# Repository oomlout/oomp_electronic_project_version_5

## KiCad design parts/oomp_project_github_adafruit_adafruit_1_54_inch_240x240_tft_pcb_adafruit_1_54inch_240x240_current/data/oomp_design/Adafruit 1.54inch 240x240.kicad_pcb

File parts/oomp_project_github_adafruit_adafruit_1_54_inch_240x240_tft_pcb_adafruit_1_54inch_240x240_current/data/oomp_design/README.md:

# OOMP KiCad design copy

Open `Adafruit 1.54inch 240x240.kicad_pro` (or the `.kicad_pcb` / `.kicad_sch`) in KiCad. Local OOMP libraries are under `libraries/`. Original inputs are preserved in [../original/](../original/).

Only verified unchanged installed KiCad defaults were renamed. Modified, custom, unmatched and unavailable items remain unchanged. Soldering variants are never swapped during conversion. Existing pad coordinates, nets and UUIDs are preserved.

See [conversion_report.yaml](conversion_report.yaml) for every conversion and skip. Copy this directory before editing; regeneration refuses to overwrite edited design files.

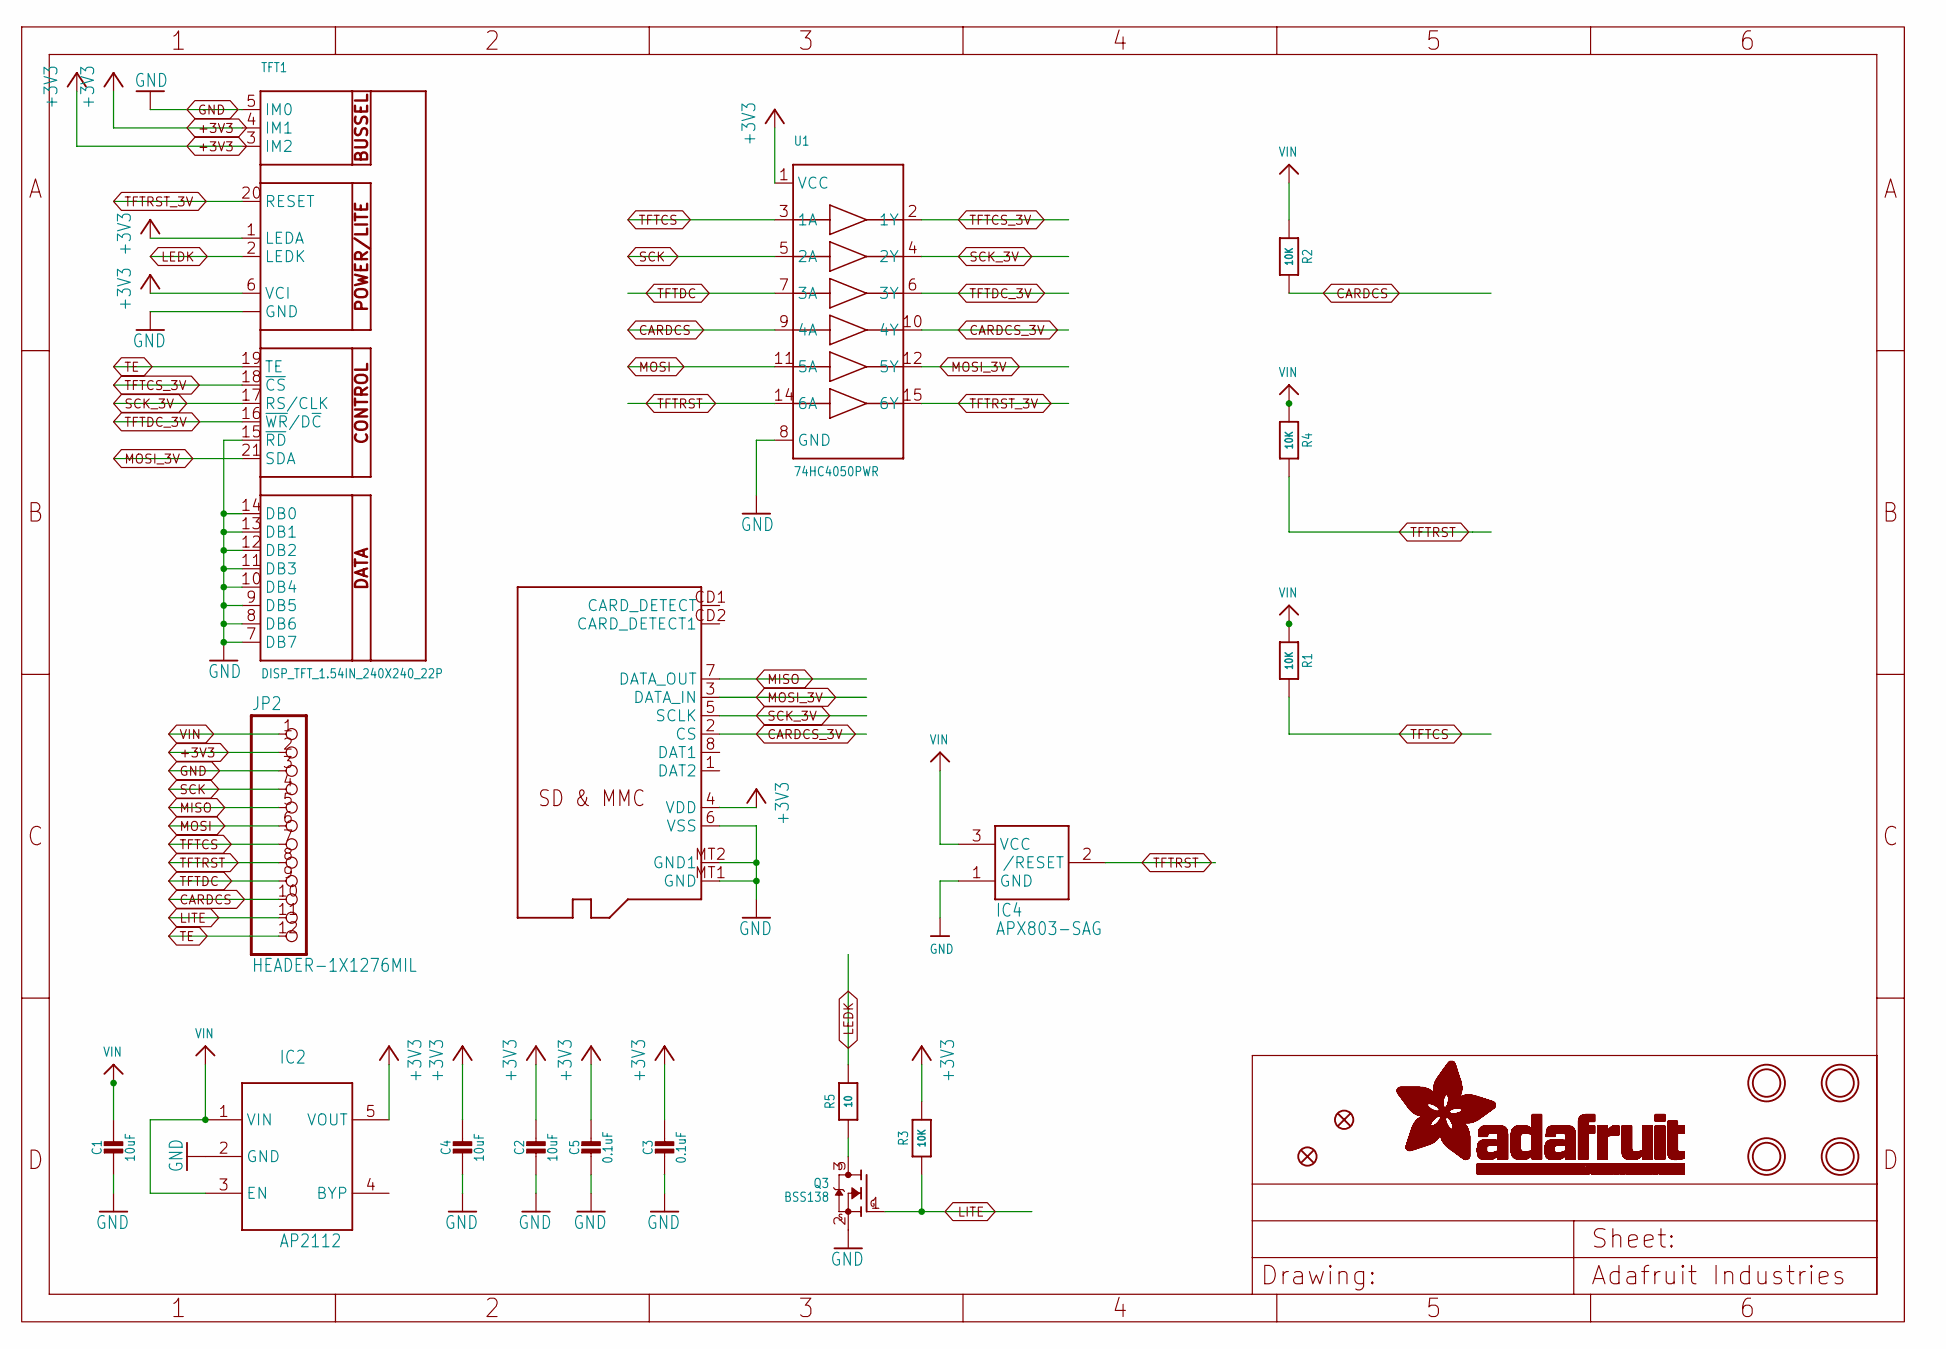
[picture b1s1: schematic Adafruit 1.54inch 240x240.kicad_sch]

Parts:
C1, C2, C4: 10uF; 0805-NO
C3, C5: 0.1uF; 0603-NO
IC2: AP2112; SOT23-5L
IC4: APX803-SAG; SOT23
JP2: HEADER-1X1276MIL; 1X12_ROUND_76MIL
Q2: MICROSD
Q3: BSS138; SOT23-WIDE
R1, R2, R3, R4: 10K; 0603-NO
R5: 10; 0603-NO
TFT1: DISP_TFT_1.54IN_240X240_22P; TFT_1.54IN_240X240_22PIN
U1: 74HC4050PWR; TSSOP16
U$4, U$5: FIDUCIAL_1MM
U$7, U$8, U$9, U$10: MOUNTINGHOLE2.5; MOUNTINGHOLE_2.5_PLATED

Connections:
+3V3: C2.1, C3.1, C4.1, C5.1, IC2.5 (VOUT), JP2.2, Q2.4 (VDD), R3.2, TFT1.1 (LEDA), TFT1.3 (IM2), TFT1.4 (IM1), TFT1.6 (VCI), U1.1 (VCC)
CARDCS: JP2.10, R2.1, U1.9 (4A)
CARDCS_3V: Q2.2 (CS), U1.10 (4Y)
GND: C1.2, C2.2, C3.2, C4.2, C5.2, IC2.2 (GND), IC4.1 (GND), JP2.3, Q2.6 (VSS), Q2.MT1 (GND), Q2.MT2 (GND1), Q3.2 (S), TFT1.5 (IM0), TFT1.7 (DB7), TFT1.8 (DB6), TFT1.9 (DB5), TFT1.10 (DB4), TFT1.11 (DB3), TFT1.12 (DB2), TFT1.13 (DB1), TFT1.14 (DB0), TFT1.15 (~RD), TFT1.22 (GND), TFT1.SUPPORT1 (GND), TFT1.SUPPORT2 (GND), U1.8 (GND)
LEDK: R5.2, TFT1.2 (LEDK)
LITE: JP2.11, Q3.1 (G), R3.1
MISO: JP2.5, Q2.7 (DATA_OUT)
MOSI: JP2.6, U1.11 (5A)
MOSI_3V: Q2.3 (DATA_IN), TFT1.21 (SDA), U1.12 (5Y)
unnamed: Q3.3 (D), R5.1
SCK: JP2.4, U1.5 (2A)
SCK_3V: Q2.5 (SCLK), TFT1.17 (RS/CLK), U1.4 (2Y)
TE: JP2.12, TFT1.19 (TE)
TFTCS: JP2.7, R1.1, U1.3 (1A)
TFTCS_3V: TFT1.18 (~CS), U1.2 (1Y)
TFTDC: JP2.9, U1.7 (3A)
TFTDC_3V: TFT1.16 (~WR/D~C), U1.6 (3Y)
TFTRST: IC4.2 (/RESET), JP2.8, R4.1, U1.14 (6A)
TFTRST_3V: TFT1.20 (RESET), U1.15 (6Y)
VIN: C1.1, IC2.1 (VIN), IC2.3 (EN), IC4.3 (VCC), JP2.1, R1.2, R2.2, R4.2

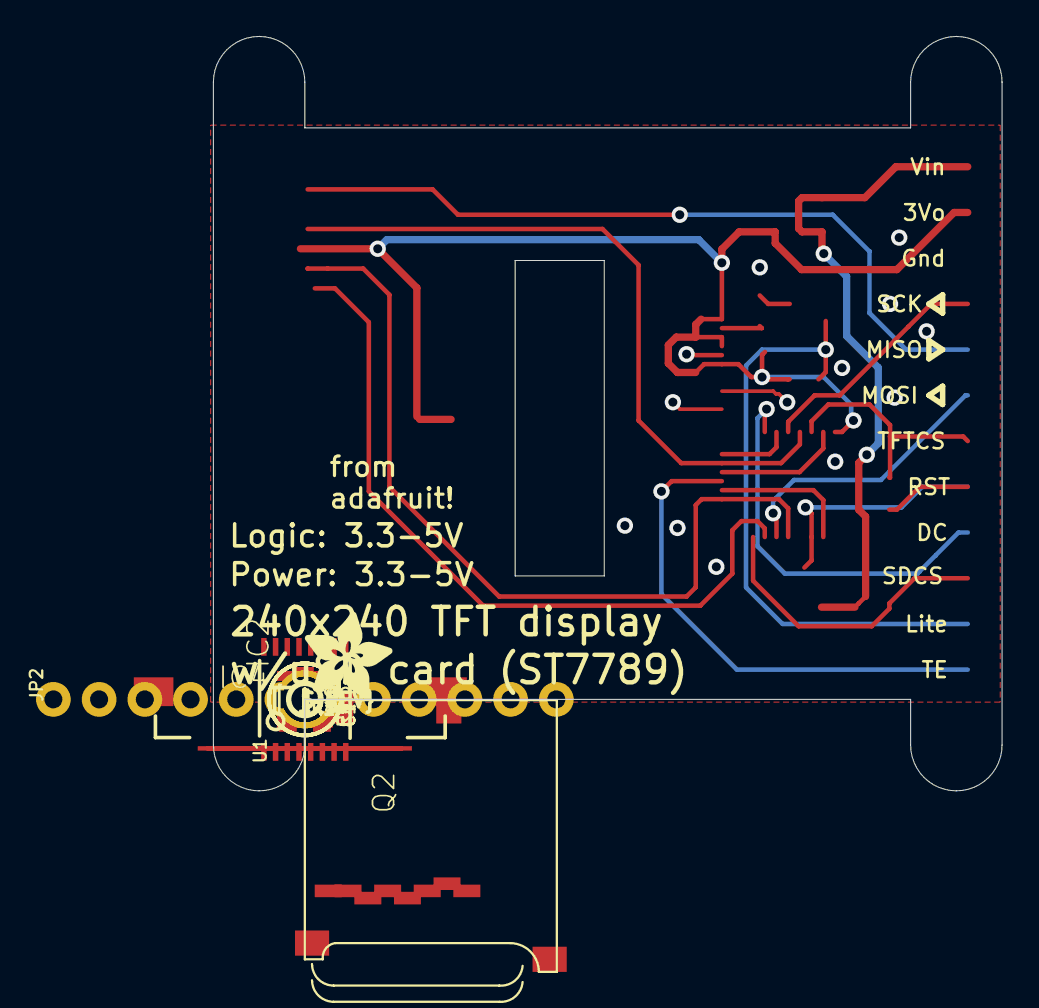
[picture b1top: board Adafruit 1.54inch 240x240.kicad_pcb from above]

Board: 16 copper layers, 43.8 x 41.9 mm, 25 parts (1 on the bottom side), 20 nets.

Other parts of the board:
U$1: ADAFRUIT_5MM
U$2: PCBFEAT-REV-040

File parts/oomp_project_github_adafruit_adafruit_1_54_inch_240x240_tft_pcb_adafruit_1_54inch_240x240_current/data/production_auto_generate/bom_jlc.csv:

Comment,Designator,Footprint,LCSC Part #
,JP2,Adafruit 1.54inch 240x240-import-fps:1X12_ROUND_76MIL,C7501588
,U$1,Adafruit 1.54inch 240x240-import-fps:ADAFRUIT_5MM,
,U$2,Adafruit 1.54inch 240x240-import-fps:PCBFEAT-REV-040,
0.1uF,"C3,C5",Adafruit 1.54inch 240x240-import-fps:0603-NO,C14663
10,R5,Adafruit 1.54inch 240x240-import-fps:0603-NO,C22859
10K,"R1,R2,R3,R4",Adafruit 1.54inch 240x240-import-fps:0603-NO,C98220
10uF,"C1,C2,C4",Adafruit 1.54inch 240x240-import-fps:0805-NO,
74HC4050PWR,U1,Adafruit 1.54inch 240x240-import-fps:TSSOP16,
AP2112,IC2,Adafruit 1.54inch 240x240-import-fps:SOT23-5L,
APX803-SAG,IC4,Adafruit 1.54inch 240x240-import-fps:SOT23,
BSS138,Q3,Adafruit 1.54inch 240x240-import-fps:SOT23-WIDE,C52895
DISP_TFT_1.54IN_240X240_22P,TFT1,Adafruit 1.54inch 240x240-import-fps:TFT_1.54IN_240X240_22PIN,
FIDUCIAL_1MM,"U$4,U$5",Adafruit 1.54inch 240x240-import-fps:FIDUCIAL_1MM,
MICROSD,Q2,Adafruit 1.54inch 240x240-import-fps:MICROSD,

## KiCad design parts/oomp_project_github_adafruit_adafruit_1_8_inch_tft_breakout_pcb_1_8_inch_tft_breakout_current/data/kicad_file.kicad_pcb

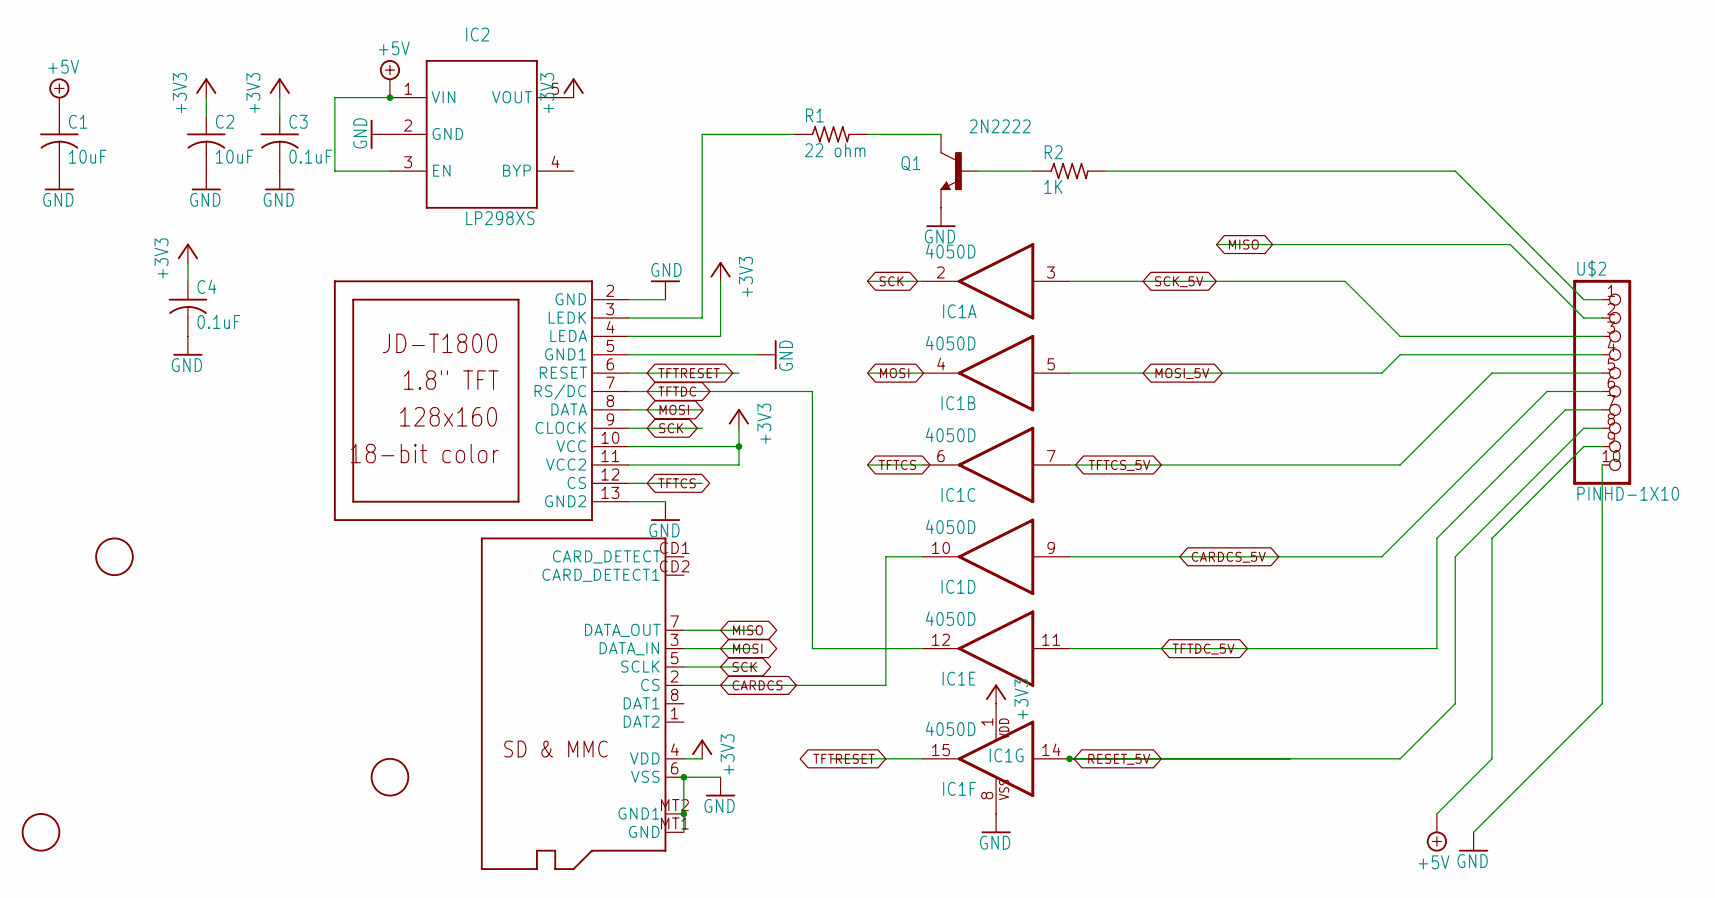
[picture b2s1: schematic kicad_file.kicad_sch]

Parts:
C1, C2: 10uF; C0805K
C3, C4: 0.1uF; C0805K
IC1: 4050D; SO16
IC2: LP298XS; SOT23-5L
Q1: 2N2222; SOT23-BEC
Q2: MICROSD
R1: 22 ohm; R0805
R2: 1K; R0805
U$1: JD-T1800
U$2: PINHD-1X10; 1X10-BIG
U$3, U$4, U$5: FIDUCIAL; FIDUCIAL_1MM

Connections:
+3V3: C2.1, C3.1, C4.1, IC1.1 (VDD), IC2.5 (VOUT), Q2.4 (VDD), U$1.4 (LEDA), U$1.10 (VCC), U$1.11 (VCC2)
+5V: C1.1, IC2.1 (VIN), IC2.3 (EN), U$2.9
CARDCS: IC1.10 (O), Q2.2 (CS)
CARDCS_5V: IC1.9 (I), U$2.6
GND: C1.2, C2.2, C3.2, C4.2, IC1.8 (VSS), IC2.2 (GND), Q1.E, Q2.6 (VSS), Q2.MT1 (GND), Q2.MT2 (GND1), U$1.2 (GND), U$1.5 (GND1), U$1.13 (GND2), U$2.10
MISO: Q2.7 (DATA_OUT), U$2.2
MOSI: IC1.4 (O), Q2.3 (DATA_IN), U$1.8 (DATA)
MOSI_5V: IC1.5 (I), U$2.4
unnamed: Q1.B, R2.1
unnamed: R1.1, U$1.3 (LEDK)
unnamed: Q1.C, R1.2
unnamed: R2.2, U$2.1
RESET_5V: IC1.14 (I), U$2.8
SCK: IC1.2 (O), Q2.5 (SCLK), U$1.9 (CLOCK)
SCK_5V: IC1.3 (I), U$2.3
TFTCS: IC1.6 (O), U$1.12 (CS)
TFTCS_5V: IC1.7 (I), U$2.5
TFTDC: IC1.12 (O), U$1.7 (RS/DC)
TFTDC_5V: IC1.11 (I), U$2.7
TFTRESET: IC1.15 (O), U$1.6 (RESET)

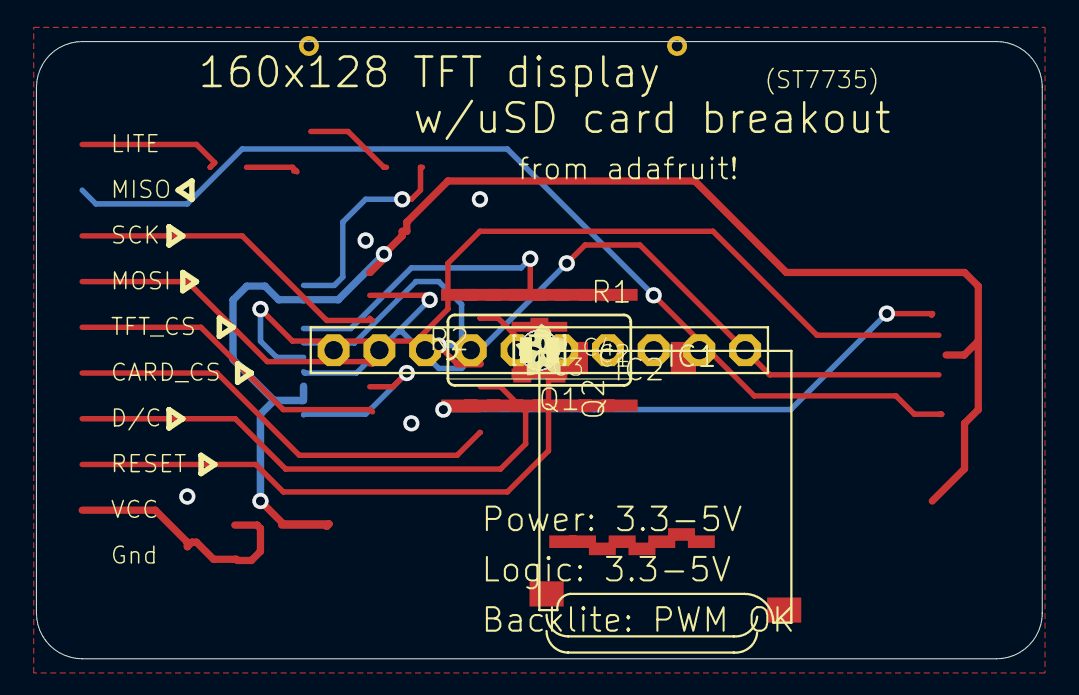
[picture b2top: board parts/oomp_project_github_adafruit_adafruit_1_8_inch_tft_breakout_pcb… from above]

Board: 16 copper layers, 55.9 x 34.3 mm, 20 parts (1 on the bottom side), 20 nets.

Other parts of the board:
U$6: ADAFRUIT200MIL
UNK_HOLE_0: dummyfp0
UNK_HOLE_1: dummyfp1
UNK_HOLE_2: dummyfp2
UNK_HOLE_3: dummyfp3

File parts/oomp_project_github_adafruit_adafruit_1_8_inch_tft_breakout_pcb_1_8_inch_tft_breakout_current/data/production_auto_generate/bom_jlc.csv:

Comment,Designator,Footprint,LCSC Part #
,U$6,jdt1800-bob-import-fps:ADAFRUIT200MIL,
0.1uF,"C3,C4",jdt1800-bob-import-fps:C0805K,
10uF,"C1,C2",jdt1800-bob-import-fps:C0805K,
1K,R2,jdt1800-bob-import-fps:R0805,C17513
22 ohm,R1,jdt1800-bob-import-fps:R0805,C2907310
2N2222,Q1,jdt1800-bob-import-fps:SOT23-BEC,
4050D,IC1,jdt1800-bob-import-fps:SO16,
FIDUCIAL,"U$3,U$4,U$5",jdt1800-bob-import-fps:FIDUCIAL_1MM,
JD-T1800,U$1,jdt1800-bob-import-fps:JD-T1800,
LP298XS,IC2,jdt1800-bob-import-fps:SOT23-5L,
MICROSD,Q2,jdt1800-bob-import-fps:MICROSD,
PINHD-1X10,U$2,jdt1800-bob-import-fps:1X10-BIG,

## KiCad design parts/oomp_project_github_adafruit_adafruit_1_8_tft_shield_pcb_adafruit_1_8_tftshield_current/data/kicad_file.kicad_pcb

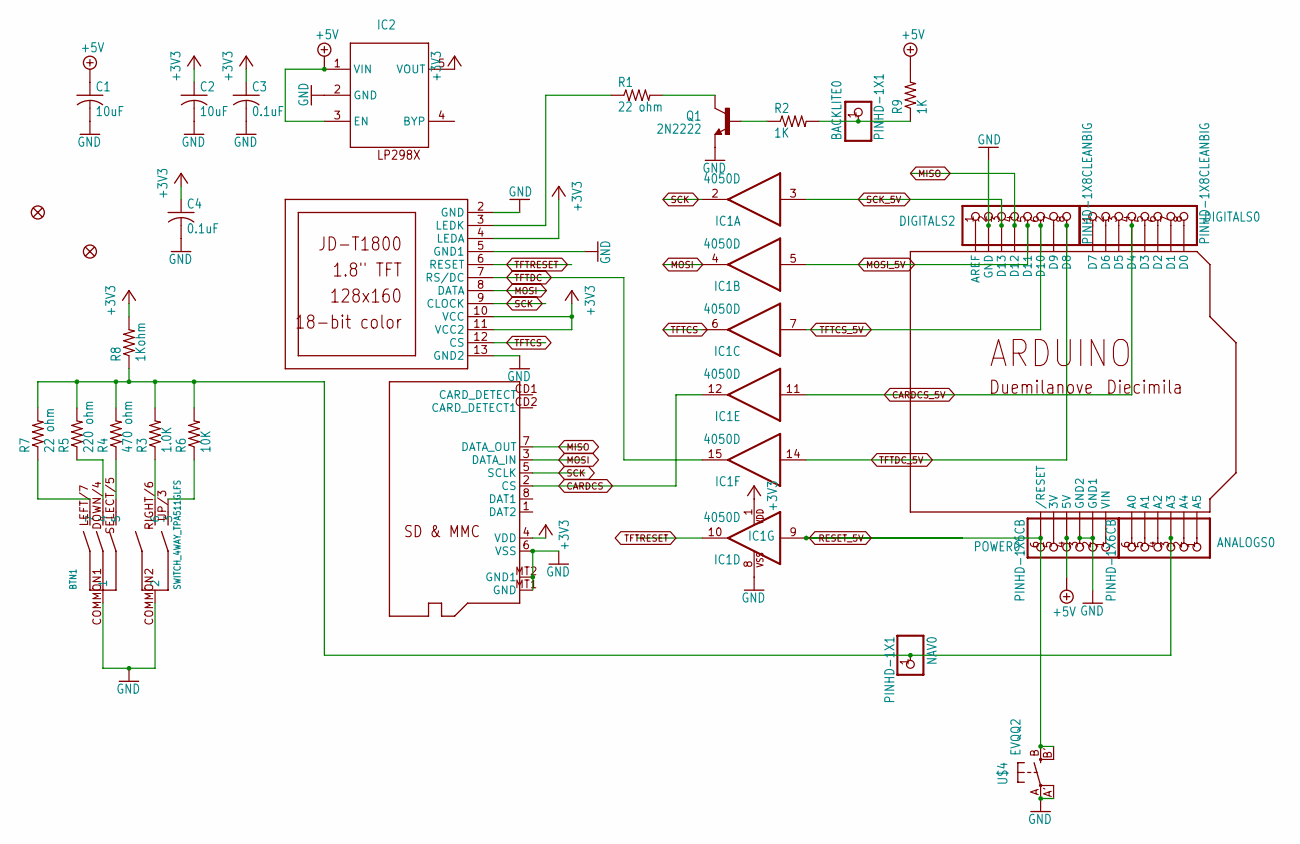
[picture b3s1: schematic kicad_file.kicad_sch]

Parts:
ANALOGS0: PINHD-1X6CB; 1X06-CLEANBIG
BACKLITE0: PINHD-1X1; 1X01
BTN1: SWITCH_4WAY_TPA511GLFS
C1, C2: 10uF; C0805K
C3, C4: 0.1uF; C0805K
DIGITALS0, DIGITALS2: PINHD-1X8CLEANBIG; 1X08-CLEANBIG
FID1, FID3: FIDUCIAL1X2.5; FIDUCIAL-1X2.5
IC1: 4050D; SO16
IC2: RT9193-33GB; SOT23-5L
NAV0: PINHD-1X1; 1X01
POWER0: PINHD-1X6CB; 1X06-CLEANBIG
Q1: 2N2222; SOT23-BEC
R1, R7: 22 ohm; R0805
R2, R9: 1K; R0805
R3: 1.0K; R0805
R4: 470 ohm; R0805
R5: 220 ohm; R0805
R6: 10K; R0805
R8: 1Kohm; R0805
U$1: JD-T1800
U$2: ARDUINOUNO; ARDUINO
U$3: MICROSD
U$4: EVQQ2; EVQ-Q2

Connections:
+3V3: C2.1, C3.1, C4.1, IC1.1 (VDD), IC2.5 (VOUT), R8.2, U$1.4 (LEDA), U$1.10 (VCC), U$1.11 (VCC2), U$3.4 (VDD)
+5V: C1.1, IC2.1 (VIN), IC2.3 (EN), POWER0.4, R9.2, U$2.5V
CARDCS: IC1.12 (O), U$3.2 (CS)
CARDCS_5V: DIGITALS0.4, IC1.11 (I), U$2.D4
GND: BTN1.COMMON1 (1), BTN1.COMMON2 (2), C1.2, C2.2, C3.2, C4.2, DIGITALS2.2, IC1.8 (VSS), IC2.2 (GND), POWER0.2, POWER0.3, Q1.E, U$1.2 (GND), U$1.5 (GND1), U$1.13 (GND2), U$2.GND, U$2.GND1, U$2.GND2, U$3.6 (VSS), U$3.MT1 (GND), U$3.MT2 (GND1), U$4.A, U$4.A' (P1)
MISO: DIGITALS2.4, U$2.D12, U$3.7 (DATA_OUT)
MOSI: IC1.4 (O), U$1.8 (DATA), U$3.3 (DATA_IN)
MOSI_5V: DIGITALS2.5, IC1.5 (I), U$2.D11
unnamed: Q1.B, R2.1
unnamed: BTN1.LEFT/7 (7), R7.1
unnamed: BTN1.DOWN/4 (4), R5.1
unnamed: R1.1, U$1.3 (LEDK)
unnamed: Q1.C, R1.2
unnamed: DIGITALS2.7, U$2.D9
unnamed: BTN1.SELECT/5 (5), R4.1
unnamed: BTN1.RIGHT/6 (6), R3.1
unnamed: BTN1.UP/3 (3), R6.1
unnamed: ANALOGS0.3, NAV0.1, R3.2, R4.2, R5.2, R6.2, R7.2, R8.1, U$2.A3
unnamed: DIGITALS0.1, U$2.D7
unnamed: DIGITALS0.2, U$2.D6
unnamed: DIGITALS0.3, U$2.D5
unnamed: DIGITALS0.5, U$2.D3
unnamed: DIGITALS0.6, U$2.D2
unnamed: DIGITALS0.7, U$2.D1
unnamed: DIGITALS0.8, U$2.D0
unnamed: DIGITALS2.1, U$2.AREF
unnamed: ANALOGS0.1, U$2.A5
unnamed: ANALOGS0.2, U$2.A4
unnamed: ANALOGS0.4, U$2.A2
unnamed: ANALOGS0.5, U$2.A1
unnamed: ANALOGS0.6, U$2.A0
unnamed: POWER0.1, U$2.VIN
unnamed: POWER0.5, U$2.3V
unnamed: BACKLITE0.1, R2.2, R9.1
RESET_5V: IC1.9 (I), POWER0.6, U$2.RESET (/RESET), U$4.B (S), U$4.B' (S1)
SCK: IC1.2 (O), U$1.9 (CLOCK), U$3.5 (SCLK)
SCK_5V: DIGITALS2.3, IC1.3 (I), U$2.D13
TFTCS: IC1.6 (O), U$1.12 (CS)
TFTCS_5V: DIGITALS2.6, IC1.7 (I), U$2.D10
TFTDC: IC1.15 (O), U$1.7 (RS/DC)
TFTDC_5V: DIGITALS2.8, IC1.14 (I), U$2.D8
TFTRESET: IC1.10 (O), U$1.6 (RESET)

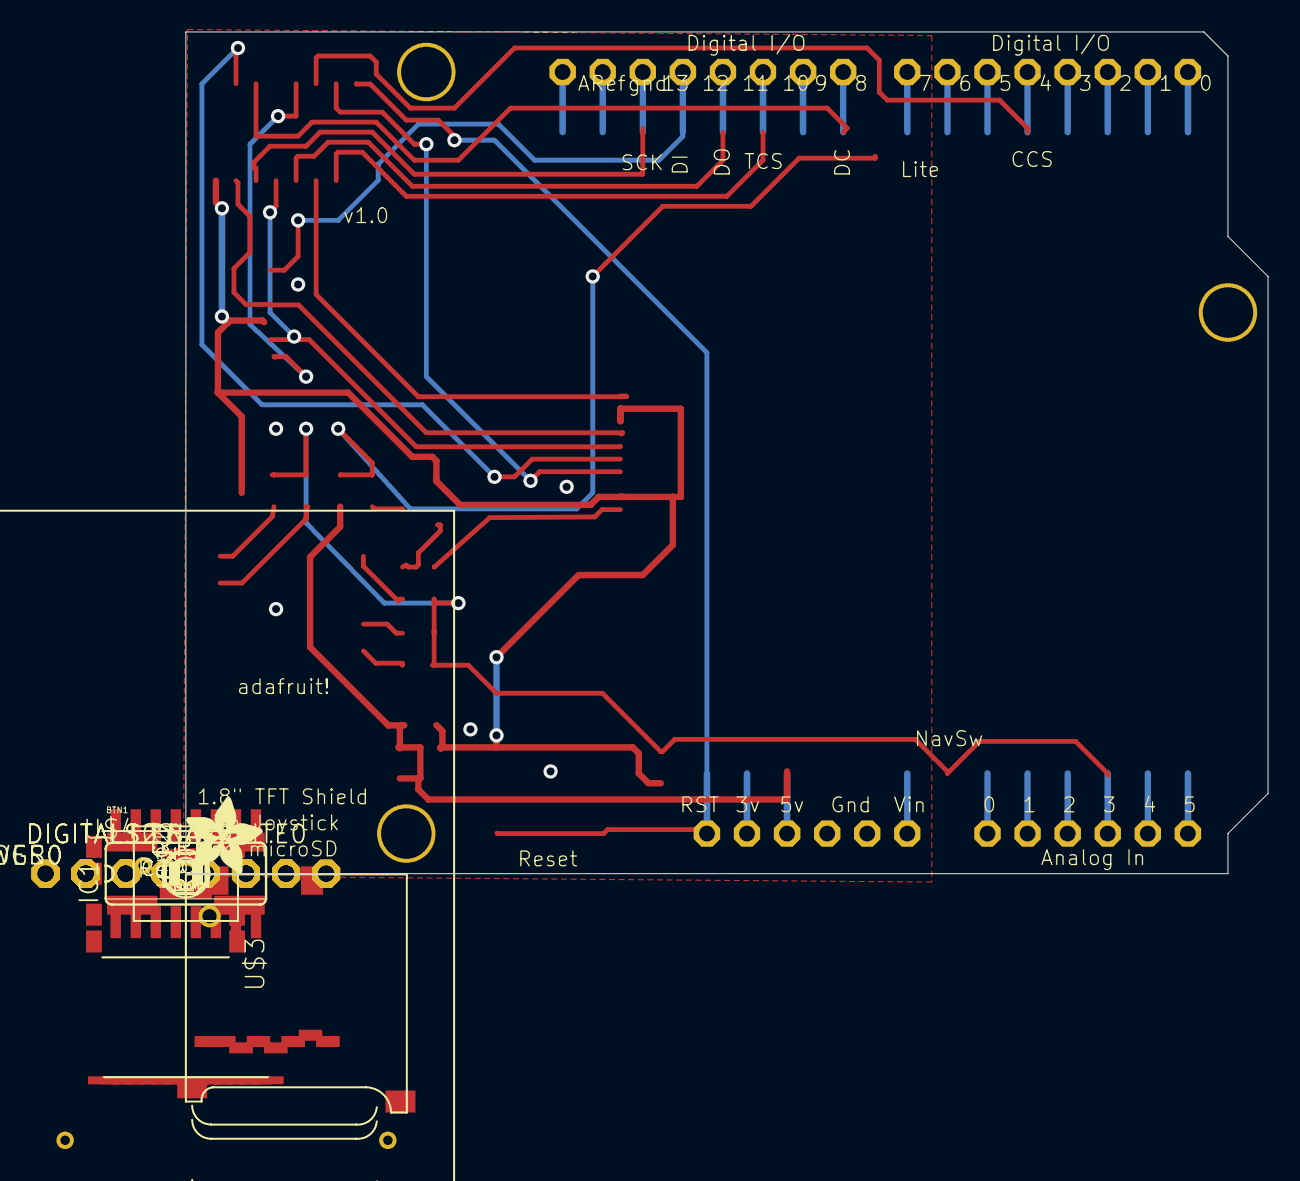
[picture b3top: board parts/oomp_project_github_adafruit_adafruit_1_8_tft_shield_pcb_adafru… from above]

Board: 16 copper layers, 68.6 x 53.3 mm, 31 parts (1 on the bottom side), 42 nets.

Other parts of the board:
U$5: ADAFRUIT_TEXT_30MM
U$6: ADAFRUIT_5MM

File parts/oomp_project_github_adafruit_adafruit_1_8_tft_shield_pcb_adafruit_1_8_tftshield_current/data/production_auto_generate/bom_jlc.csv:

Comment,Designator,Footprint,LCSC Part #
,"BACKLITE0,NAV0",Adafruit 1.8 TFTshield-import-fps:1X01,C7501259
,"ANALOGS0,POWER0",Adafruit 1.8 TFTshield-import-fps:1X06-CLEANBIG,C37208
,"DIGITALS0,DIGITALS2",Adafruit 1.8 TFTshield-import-fps:1X08-CLEANBIG,
,U$6,Adafruit 1.8 TFTshield-import-fps:ADAFRUIT_5MM,
,U$5,Adafruit 1.8 TFTshield-import-fps:ADAFRUIT_TEXT_30MM,
,BTN1,Adafruit 1.8 TFTshield-import-fps:SWITCH_4WAY_TPA511GLFS,
0.1uF,"C3,C4",Adafruit 1.8 TFTshield-import-fps:C0805K,
1.0K,R3,Adafruit 1.8 TFTshield-import-fps:R0805,C17513
10K,R6,Adafruit 1.8 TFTshield-import-fps:R0805,C17414
10uF,"C1,C2",Adafruit 1.8 TFTshield-import-fps:C0805K,
1K,"R2,R9",Adafruit 1.8 TFTshield-import-fps:R0805,C17513
1Kohm,R8,Adafruit 1.8 TFTshield-import-fps:R0805,C17513
22 ohm,"R1,R7",Adafruit 1.8 TFTshield-import-fps:R0805,C2907310
220 ohm,R5,Adafruit 1.8 TFTshield-import-fps:R0805,C2933369
2N2222,Q1,Adafruit 1.8 TFTshield-import-fps:SOT23-BEC,
4050D,IC1,Adafruit 1.8 TFTshield-import-fps:SO16,
470 ohm,R4,Adafruit 1.8 TFTshield-import-fps:R0805,C17710
ARDUINOUNO,U$2,Adafruit 1.8 TFTshield-import-fps:ARDUINO,
EVQQ2,U$4,Adafruit 1.8 TFTshield-import-fps:EVQ-Q2,
JD-T1800,U$1,Adafruit 1.8 TFTshield-import-fps:JD-T1800,
MICROSD,U$3,Adafruit 1.8 TFTshield-import-fps:MICROSD,
RT9193-33GB,IC2,Adafruit 1.8 TFTshield-import-fps:SOT23-5L,
